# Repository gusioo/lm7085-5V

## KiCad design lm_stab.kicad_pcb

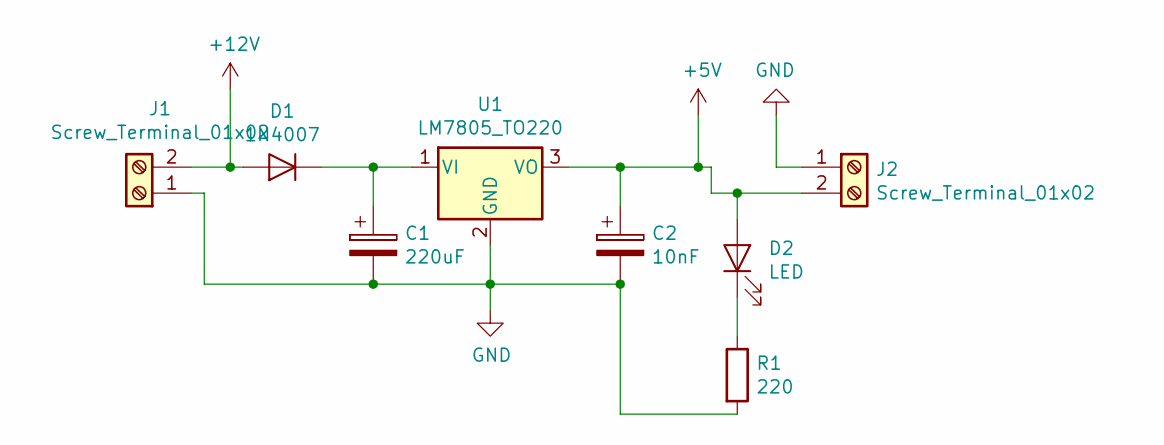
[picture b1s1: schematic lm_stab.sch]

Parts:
C1: 220uF; CP_Radial_D5.0mm_P2.00mm
C2: 10nF; CP_Radial_D5.0mm_P2.00mm
D1: 1N4007; D_DO-41_SOD81_P10.16mm_Horizontal
D2: LED; LED_D3.0mm
J1, J2: Screw_Terminal_01x02; TerminalBlock_TE_282834-2_1x02_P2.54mm_Horizontal
R1: 220; R_Axial_DIN0207_L6.3mm_D2.5mm_P7.62mm_Horizontal
U1: LM7805_TO220; TO-220-3_Horizontal_TabDown

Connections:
+5V: C2.1, D2.2 (A), J2.2, U1.3 (VO)
+12V: D1.2 (A), J1.2
GND: C1.2, C2.2, J1.1, J2.1, R1.2, U1.2 (GND)
unnamed: C1.1, D1.1 (K), U1.1 (VI)
unnamed: D2.1 (K), R1.1

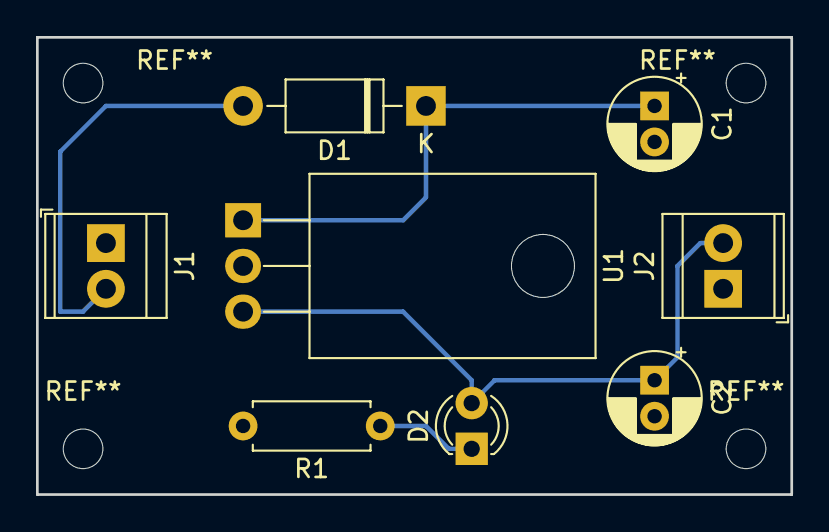
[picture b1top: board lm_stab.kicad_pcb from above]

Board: 2 copper layers, 41.9 x 25.4 mm, 8 parts (0 on the bottom side), 5 nets.

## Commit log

2021-01-05 Schematic + PCB
2021-01-07 PCB layout
